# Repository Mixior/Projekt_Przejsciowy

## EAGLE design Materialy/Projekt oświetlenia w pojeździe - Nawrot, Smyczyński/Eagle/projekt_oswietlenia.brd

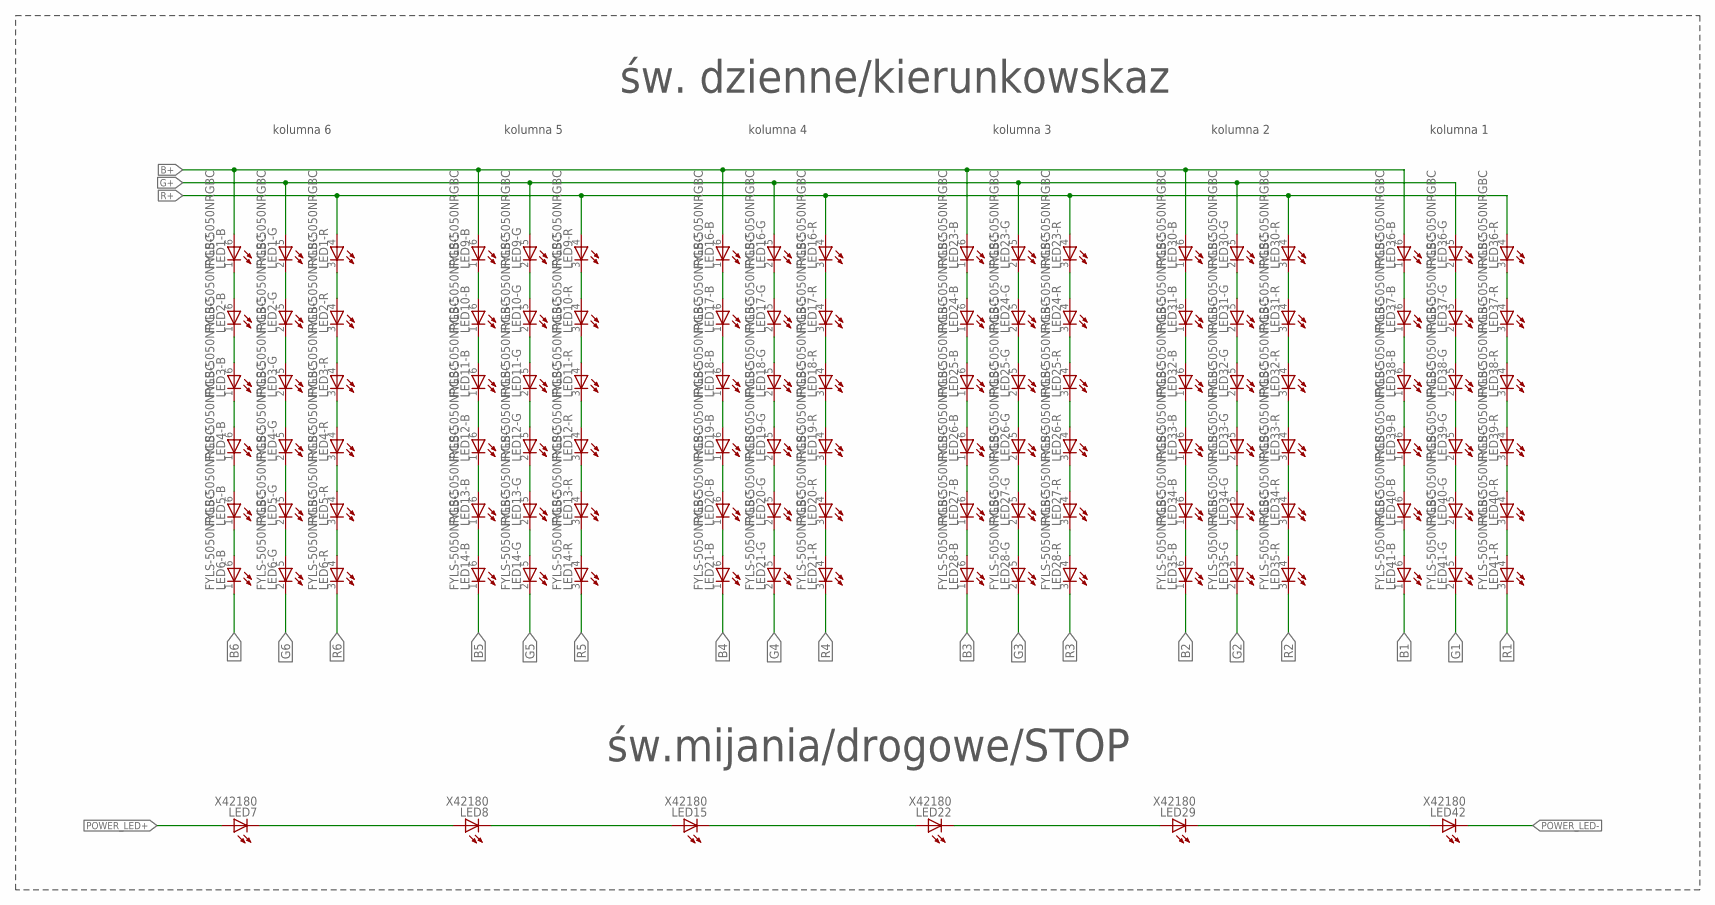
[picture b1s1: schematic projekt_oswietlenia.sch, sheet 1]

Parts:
LED1, LED2, LED3, LED4, LED5, LED6, LED9, LED10, LED11, LED12, LED13, LED14, LED16, LED17, LED18, LED19, LED20, LED21, LED23, LED24, LED25, LED26, LED27, LED28, LED30, LED31, LED32, LED33, LED34, LED35, LED36, LED37, LED38, LED39, LED40, LED41: FYLS-5050NRGBC; OVSTRGBBCR8
LED7, LED8, LED15, LED22, LED29, LED42: X42180; Z-POWER-LED-DOME-TYPE

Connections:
B1: LED41.1 (C); also elsewhere on the board
B2: LED35.1 (C); also elsewhere on the board
B3: LED28.1 (C); also elsewhere on the board
B4: LED21.1 (C); also elsewhere on the board
B5: LED14.1 (C); also elsewhere on the board
B6: LED6.1 (C); also elsewhere on the board
B+: LED1.6 (A), LED9.6 (A), LED16.6 (A), LED23.6 (A), LED30.6 (A), LED36.6 (A); also elsewhere on the board
G1: LED41.2 (C); also elsewhere on the board
G2: LED35.2 (C); also elsewhere on the board
G3: LED28.2 (C); also elsewhere on the board
G4: LED21.2 (C); also elsewhere on the board
G5: LED14.2 (C); also elsewhere on the board
G6: LED6.2 (C); also elsewhere on the board
G+: LED1.5 (A), LED9.5 (A), LED16.5 (A), LED23.5 (A), LED30.5 (A), LED36.5 (A); also elsewhere on the board
unnamed: LED13.3 (C), LED14.4 (A)
unnamed: LED13.2 (C), LED14.5 (A)
unnamed: LED13.1 (C), LED14.6 (A)
unnamed: LED12.3 (C), LED13.4 (A)
unnamed: LED12.2 (C), LED13.5 (A)
unnamed: LED12.1 (C), LED13.6 (A)
unnamed: LED11.1 (C), LED12.6 (A)
unnamed: LED11.2 (C), LED12.5 (A)
unnamed: LED11.3 (C), LED12.4 (A)
unnamed: LED10.3 (C), LED11.4 (A)
unnamed: LED10.2 (C), LED11.5 (A)
unnamed: LED29.C, LED42.A
unnamed: LED10.1 (C), LED11.6 (A)
unnamed: LED9.3 (C), LED10.4 (A)
unnamed: LED9.2 (C), LED10.5 (A)
unnamed: LED9.1 (C), LED10.6 (A)
unnamed: LED5.3 (C), LED6.4 (A)
unnamed: LED5.2 (C), LED6.5 (A)
unnamed: LED5.1 (C), LED6.6 (A)
unnamed: LED4.3 (C), LED5.4 (A)
unnamed: LED4.2 (C), LED5.5 (A)
unnamed: LED4.1 (C), LED5.6 (A)
unnamed: LED3.1 (C), LED4.6 (A)
unnamed: LED3.2 (C), LED4.5 (A)
unnamed: LED3.3 (C), LED4.4 (A)
unnamed: LED2.3 (C), LED3.4 (A)
unnamed: LED2.2 (C), LED3.5 (A)
unnamed: LED2.1 (C), LED3.6 (A)
unnamed: LED1.3 (C), LED2.4 (A)
unnamed: LED1.2 (C), LED2.5 (A)
unnamed: LED1.1 (C), LED2.6 (A)
unnamed: LED27.3 (C), LED28.4 (A)
unnamed: LED27.2 (C), LED28.5 (A)
unnamed: LED27.1 (C), LED28.6 (A)
unnamed: LED26.3 (C), LED27.4 (A)
unnamed: LED26.2 (C), LED27.5 (A)
unnamed: LED26.1 (C), LED27.6 (A)
unnamed: LED25.1 (C), LED26.6 (A)
unnamed: LED25.2 (C), LED26.5 (A)
unnamed: LED25.3 (C), LED26.4 (A)
unnamed: LED24.3 (C), LED25.4 (A)
unnamed: LED24.2 (C), LED25.5 (A)
unnamed: LED24.1 (C), LED25.6 (A)
unnamed: LED23.3 (C), LED24.4 (A)
unnamed: LED23.2 (C), LED24.5 (A)
unnamed: LED23.1 (C), LED24.6 (A)
unnamed: LED20.3 (C), LED21.4 (A)
unnamed: LED20.2 (C), LED21.5 (A)
unnamed: LED20.1 (C), LED21.6 (A)
unnamed: LED19.3 (C), LED20.4 (A)
unnamed: LED19.2 (C), LED20.5 (A)
unnamed: LED19.1 (C), LED20.6 (A)
unnamed: LED18.1 (C), LED19.6 (A)
unnamed: LED18.2 (C), LED19.5 (A)
unnamed: LED18.3 (C), LED19.4 (A)
unnamed: LED17.3 (C), LED18.4 (A)
unnamed: LED17.2 (C), LED18.5 (A)
unnamed: LED17.1 (C), LED18.6 (A)
unnamed: LED16.3 (C), LED17.4 (A)
unnamed: LED16.2 (C), LED17.5 (A)
unnamed: LED16.1 (C), LED17.6 (A)
unnamed: LED40.3 (C), LED41.4 (A)
unnamed: LED40.2 (C), LED41.5 (A)
unnamed: LED40.1 (C), LED41.6 (A)
unnamed: LED39.3 (C), LED40.4 (A)
unnamed: LED39.2 (C), LED40.5 (A)
unnamed: LED39.1 (C), LED40.6 (A)
unnamed: LED38.1 (C), LED39.6 (A)
unnamed: LED38.2 (C), LED39.5 (A)
unnamed: LED38.3 (C), LED39.4 (A)
unnamed: LED37.3 (C), LED38.4 (A)
unnamed: LED37.2 (C), LED38.5 (A)
unnamed: LED37.1 (C), LED38.6 (A)
unnamed: LED36.3 (C), LED37.4 (A)
unnamed: LED36.2 (C), LED37.5 (A)
unnamed: LED36.1 (C), LED37.6 (A)
unnamed: LED34.3 (C), LED35.4 (A)
unnamed: LED34.2 (C), LED35.5 (A)
unnamed: LED34.1 (C), LED35.6 (A)
unnamed: LED33.3 (C), LED34.4 (A)
unnamed: LED33.2 (C), LED34.5 (A)
unnamed: LED33.1 (C), LED34.6 (A)
unnamed: LED32.1 (C), LED33.6 (A)
unnamed: LED32.2 (C), LED33.5 (A)
unnamed: LED32.3 (C), LED33.4 (A)
unnamed: LED31.3 (C), LED32.4 (A)
unnamed: LED31.2 (C), LED32.5 (A)
unnamed: LED31.1 (C), LED32.6 (A)
unnamed: LED30.3 (C), LED31.4 (A)
unnamed: LED30.2 (C), LED31.5 (A)
unnamed: LED30.1 (C), LED31.6 (A)
unnamed: LED22.C, LED29.A
unnamed: LED15.C, LED22.A
unnamed: LED8.C, LED15.A
unnamed: LED7.C, LED8.A
POWER_LED+: LED7.A; also elsewhere on the board
POWER_LED-: LED42.C; also elsewhere on the board
R1: LED41.3 (C); also elsewhere on the board
R2: LED35.3 (C); also elsewhere on the board
R3: LED28.3 (C); also elsewhere on the board
R4: LED21.3 (C); also elsewhere on the board
R5: LED14.3 (C); also elsewhere on the board
R6: LED6.3 (C); also elsewhere on the board
R+: LED1.4 (A), LED9.4 (A), LED16.4 (A), LED23.4 (A), LED30.4 (A), LED36.4 (A); also elsewhere on the board

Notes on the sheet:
św. dzienne/kierunkowskaz
kolumna 6
kolumna 5
kolumna 4
kolumna 3
kolumna 2
kolumna 1
św.mijania/drogowe/STOP

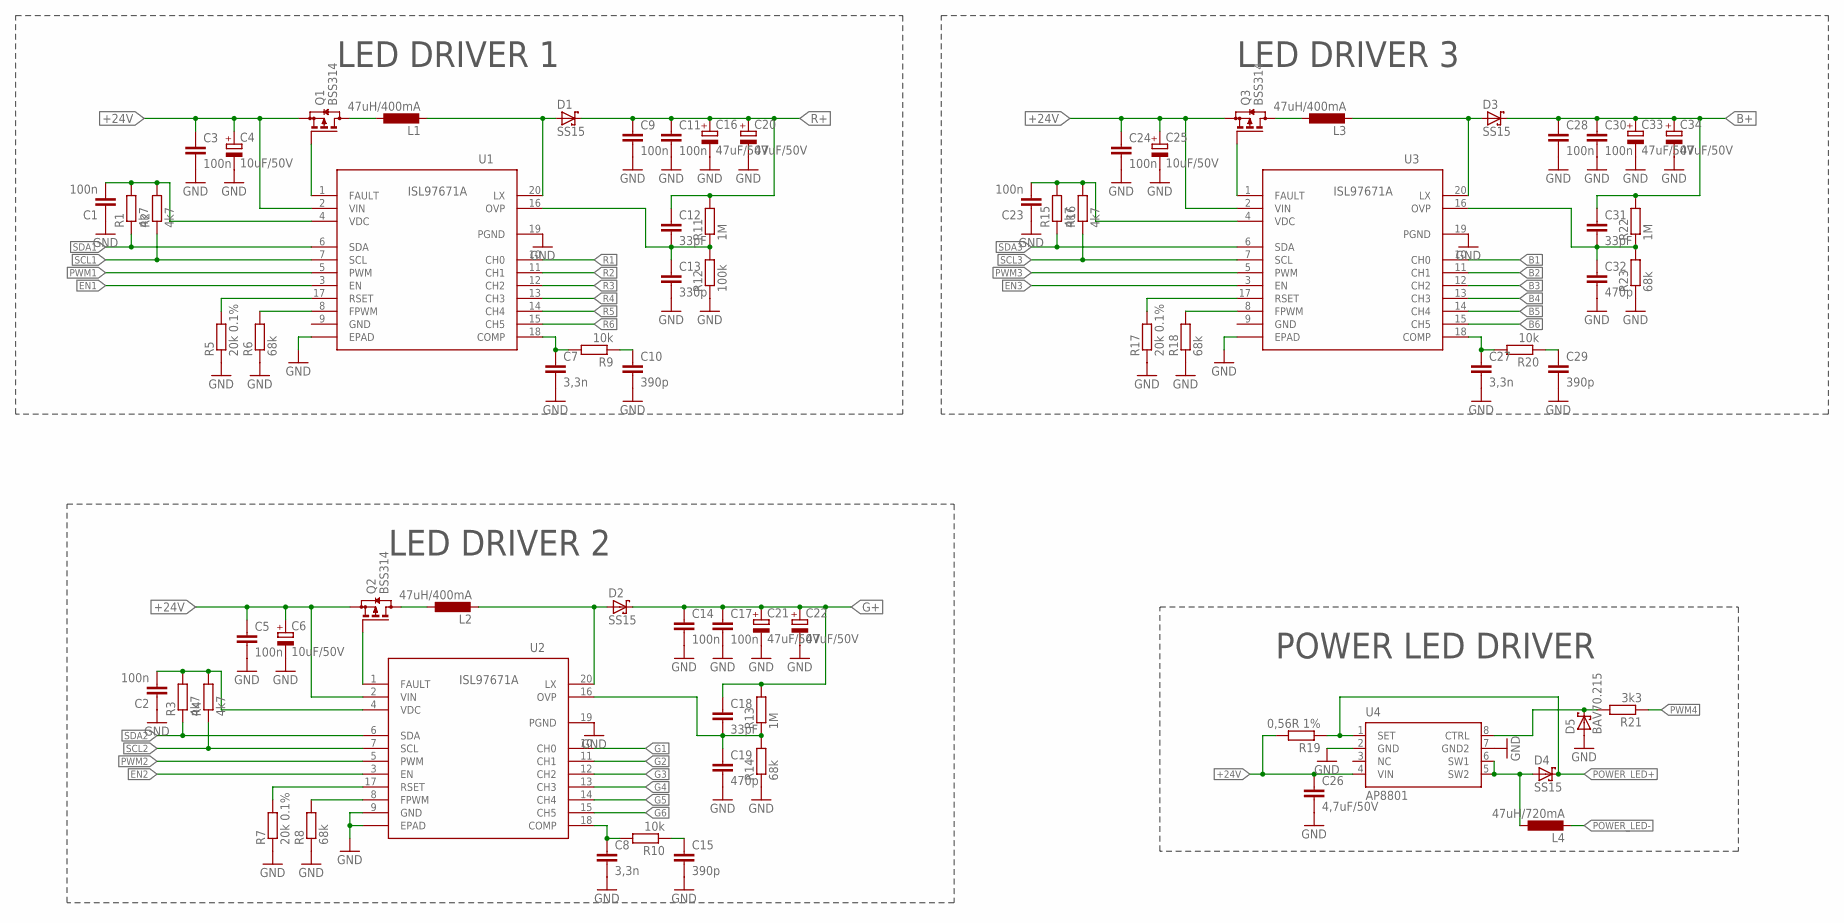
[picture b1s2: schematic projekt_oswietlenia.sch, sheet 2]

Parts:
C1, C2, C3, C5, C9, C11, C14, C17, C23, C24, C28, C30: 100n; C0603
C4, C6, C25: 10uF/50V; 153CLV-0605
C7, C8, C27: 3,3n; C0603
C10, C15, C29: 390p; C0603
C12, C18, C31: 33pF; C0603
C13: 330p; C0603
C16, C20, C21, C22, C33, C34: 47uF/50V; 153CLV-0605
C19, C32: 470p; C0603
C26: 4,7uF/50V; C0603
D1, D2, D3, D4: SS15; DO-214AC
D5: BAV70.215; SOT23
L1, L2, L3: 47uH/400mA; POWER-CHOKE_WE-TPC
L4: 47uH/720mA; POWER-CHOKE_WE-TPC
Q1, Q2, Q3: BSS314; SOT23
R1, R2, R3, R4, R15, R16: 4k7; R0603
R5, R7, R17: 20k 0.1%; R0603
R6, R8, R14, R18, R23: 68k; R0603
R9, R10, R20: 10k; R0603
R11, R13, R22: 1M; R0603
R12: 100k; R0603
R19: 0,56R 1%; R0603
R21: 3k3; R0603
U1, U2, U3: ISL97671A; QFN20
U4: AP8801; SOP-08

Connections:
+24V: C3.1, C4.+, C5.1, C6.+, C24.1, C25.+, C26.1, Q1.2 (S), Q2.2 (S), Q3.2 (S), R19.2, U1.2 (VIN), U2.2 (VIN), U3.2 (VIN), U4.4 (VIN); also elsewhere on the board
B1: U3.10 (CH0); also elsewhere on the board
B2: U3.11 (CH1); also elsewhere on the board
B3: U3.12 (CH2); also elsewhere on the board
B4: U3.13 (CH3); also elsewhere on the board
B5: U3.14 (CH4); also elsewhere on the board
B6: U3.15 (CH5); also elsewhere on the board
B+: C28.1, C30.1, C31.1, C33.+, C34.+, D3.C, R22.2; also elsewhere on the board
EN1: U1.3 (EN); also elsewhere on the board
EN2: U2.3 (EN); also elsewhere on the board
EN3: U3.3 (EN); also elsewhere on the board
G1: U2.10 (CH0); also elsewhere on the board
G2: U2.11 (CH1); also elsewhere on the board
G3: U2.12 (CH2); also elsewhere on the board
G4: U2.13 (CH3); also elsewhere on the board
G5: U2.14 (CH4); also elsewhere on the board
G6: U2.15 (CH5); also elsewhere on the board
G+: C14.1, C17.1, C18.1, C21.+, C22.+, D2.C, R13.2; also elsewhere on the board
GND: C1.1, C2.1, C3.2, C4.-, C5.2, C6.-, C7.2, C8.2, C9.2, C10.2, C11.2, C13.2, C14.2, C15.2, C16.-, C17.2, C19.2, C20.-, C21.-, C22.-, C23.1, C24.2, C25.-, C26.2, C27.2, C28.2, C29.2, C30.2, C32.2, C33.-, C34.-, D5.1 (A), R5.1, R6.1, R7.1, R8.1, R12.1, R14.1, R17.1, R18.1, R23.1, U1.9 (GND), U1.19 (PGND), U1.EPAD, U2.9 (GND), U2.19 (PGND), U2.EPAD, U3.9 (GND), U3.19 (PGND), U3.EPAD, U4.2 (GND), U4.7 (GND2); also elsewhere on the board
unnamed: D4.A, L4.1, U4.5 (SW2), U4.6 (SW1)
unnamed: D5.3 (C), R21.2, U4.8 (CTRL)
unnamed: Q3.1 (G), U3.1 (FAULT)
unnamed: L3.1, Q3.3 (D)
unnamed: D3.A, L3.2, U3.20 (LX)
unnamed: C31.2, C32.1, R22.1, R23.2, U3.16 (OVP)
unnamed: C27.1, R20.2, U3.18 (COMP)
unnamed: C29.1, R20.1
unnamed: R18.2, U3.8 (FPWM)
unnamed: R17.2, U3.17 (RSET)
unnamed: Q1.1 (G), U1.1 (FAULT)
unnamed: L1.1, Q1.3 (D)
unnamed: D1.A, L1.2, U1.20 (LX)
unnamed: C12.2, C13.1, R11.1, R12.2, U1.16 (OVP)
unnamed: C7.1, R9.2, U1.18 (COMP)
unnamed: C10.1, R9.1
unnamed: R6.2, U1.8 (FPWM)
unnamed: C23.2, R15.2, R16.2, U3.4 (VDC)
unnamed: R5.2, U1.17 (RSET)
unnamed: C1.2, R1.2, R2.2, U1.4 (VDC)
unnamed: Q2.1 (G), U2.1 (FAULT)
unnamed: L2.1, Q2.3 (D)
unnamed: D2.A, L2.2, U2.20 (LX)
unnamed: C18.2, C19.1, R13.1, R14.2, U2.16 (OVP)
unnamed: C8.1, R10.2, U2.18 (COMP)
unnamed: C15.1, R10.1
unnamed: R8.2, U2.8 (FPWM)
unnamed: R7.2, U2.17 (RSET)
unnamed: C2.2, R3.2, R4.2, U2.4 (VDC)
POWER_LED+: D4.C, R19.1, U4.1 (SET); also elsewhere on the board
POWER_LED-: L4.2; also elsewhere on the board
PWM1: U1.5 (PWM); also elsewhere on the board
PWM2: U2.5 (PWM); also elsewhere on the board
PWM3: U3.5 (PWM); also elsewhere on the board
PWM4: R21.1; also elsewhere on the board
R1: U1.10 (CH0); also elsewhere on the board
R2: U1.11 (CH1); also elsewhere on the board
R3: U1.12 (CH2); also elsewhere on the board
R4: U1.13 (CH3); also elsewhere on the board
R5: U1.14 (CH4); also elsewhere on the board
R6: U1.15 (CH5); also elsewhere on the board
R+: C9.1, C11.1, C12.1, C16.+, C20.+, D1.C, R11.2; also elsewhere on the board
SCL1: R2.1, U1.7 (SCL); also elsewhere on the board
SCL2: R4.1, U2.7 (SCL); also elsewhere on the board
SCL3: R16.1, U3.7 (SCL); also elsewhere on the board
SDA1: R1.1, U1.6 (SDA); also elsewhere on the board
SDA2: R3.1, U2.6 (SDA); also elsewhere on the board
SDA3: R15.1, U3.6 (SDA); also elsewhere on the board

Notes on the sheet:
LED DRIVER 2
LED DRIVER 3
POWER LED DRIVER
LED DRIVER 1

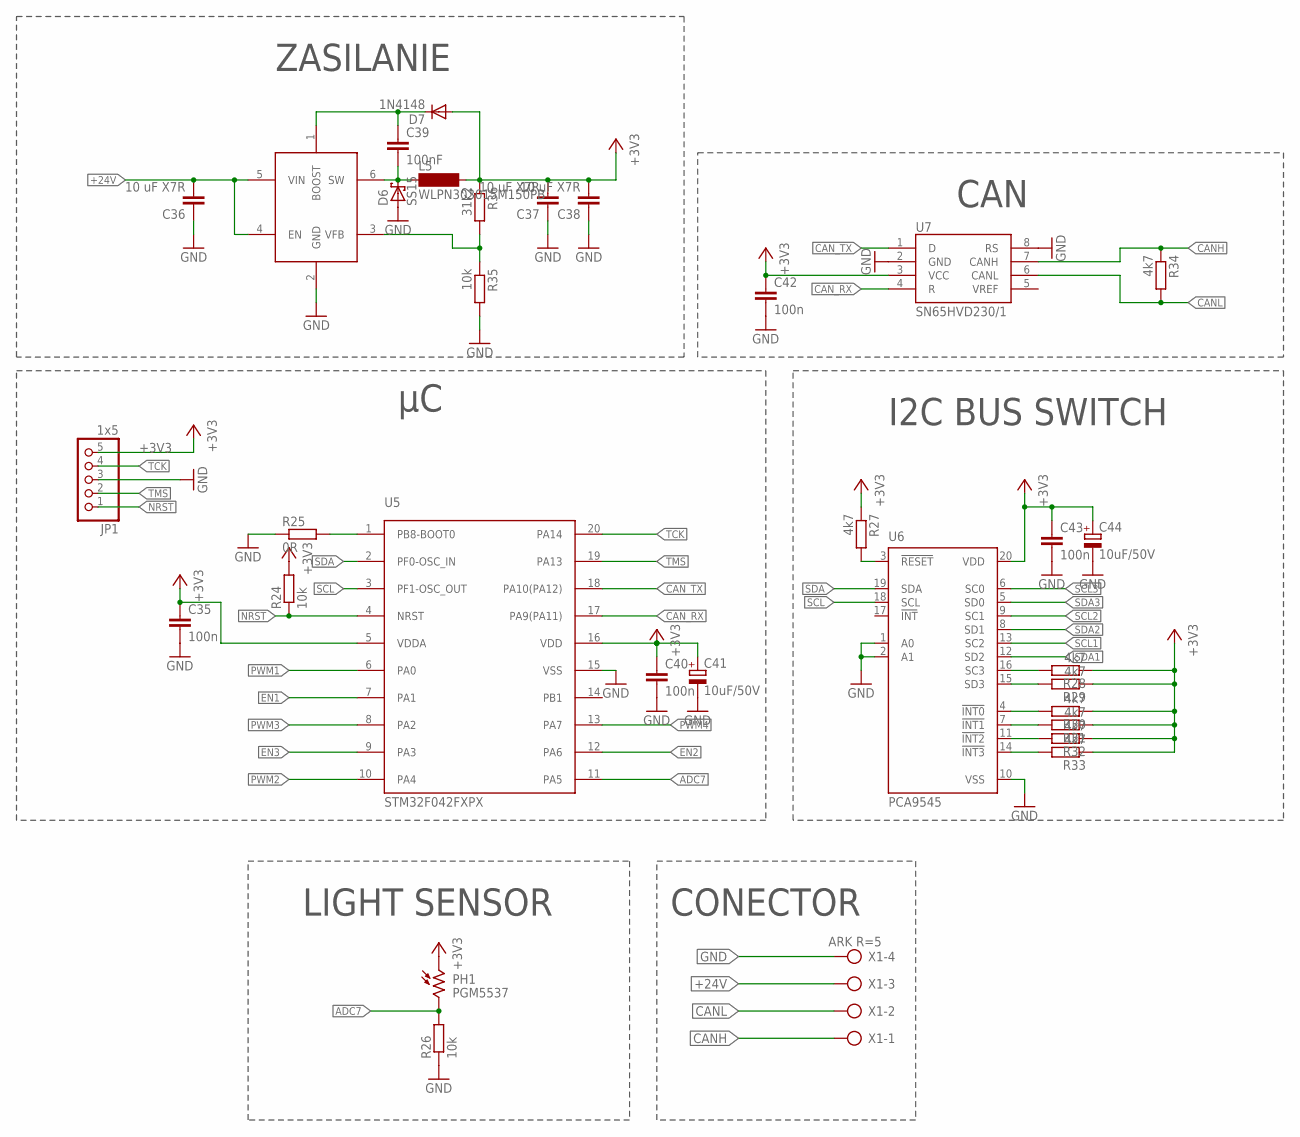
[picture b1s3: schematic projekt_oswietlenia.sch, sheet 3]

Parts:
C35, C40, C42, C43: 100n; C0603
C36, C37, C38: 10 uF X7R; C0603
C39: 100nF; C0603
C41, C44: 10uF/50V; 153CLV-0605
D6: SS15; DO-214AC
D7: 1N4148; SMB
IC1: MCP16301/H; SOT23-6
JP1: 1x5; 1X05
L5: WLPN303015M150PB; MS50
PH1: PGM5537; VT800
R24, R26, R35: 10k; R0603
R25: 0R; R0603
R27, R28, R29, R30, R31, R32, R33, R34: 4k7; R0603
R36: 31k2; R0603
U5: STM32F042FXPX; TSSOP20
U6: PCA9545; SO20W
U7: SN65HVD230/1; SO8
X1: ARK R=5; AK500/4

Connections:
+3V3: C35.1, C37.2, C38.2, C40.1, C41.+, C42.1, C43.1, C44.+, D7.A, JP1.5, L5.2, PH1.1, R24.2, R27.1, R28.1, R29.1, R30.1, R31.1, R32.1, R33.1, R36.1, U5.5 (VDDA), U5.16 (VDD), U6.20 (VDD), U7.3 (VCC)
+24V: C36.2, IC1.4 (EN), IC1.5 (VIN), X1.3; also elsewhere on the board
ADC7: PH1.2, R26.2, U5.11 (PA5)
CANH: R34.1, U7.7 (CANH), X1.1
CANL: R34.2, U7.6 (CANL), X1.2
CAN_RX: U5.17 (PA9(PA11)), U7.4 (R)
CAN_TX: U5.18 (PA10(PA12)), U7.1 (D)
EN1: U5.7 (PA1); also elsewhere on the board
EN2: U5.12 (PA6); also elsewhere on the board
EN3: U5.9 (PA3); also elsewhere on the board
GND: C35.2, C36.1, C37.1, C38.1, C40.2, C41.-, C42.2, C43.2, C44.-, D6.A, IC1.2 (GND), JP1.3, R25.1, R26.1, R35.2, U5.15 (VSS), U6.1 (A0), U6.2 (A1), U6.10 (VSS), U7.2 (GND), U7.8 (RS), X1.4; also elsewhere on the board
unnamed: C39.1, D7.C, IC1.1 (BOOST)
unnamed: R33.2, U6.14 (!INT3)
unnamed: R32.2, U6.11 (!INT2)
unnamed: R31.2, U6.7 (!INT1)
unnamed: R30.2, U6.4 (!INT0)
unnamed: R29.2, U6.15 (SD3)
unnamed: R28.2, U6.16 (SC3)
unnamed: R27.2, U6.3 (!RESET)
unnamed: C39.2, D6.C, IC1.6 (SW), L5.1
unnamed: IC1.3 (VFB), R35.1, R36.2
unnamed: R25.2, U5.1 (PB8-BOOT0)
NRST: JP1.1, R24.1, U5.4 (NRST)
PWM1: U5.6 (PA0); also elsewhere on the board
PWM2: U5.10 (PA4); also elsewhere on the board
PWM3: U5.8 (PA2); also elsewhere on the board
PWM4: U5.13 (PA7); also elsewhere on the board
SCL: U5.3 (PF1-OSC_OUT), U6.18 (SCL)
SCL1: U6.13 (SC2); also elsewhere on the board
SCL2: U6.9 (SC1); also elsewhere on the board
SCL3: U6.6 (SC0); also elsewhere on the board
SDA: U5.2 (PF0-OSC_IN), U6.19 (SDA)
SDA1: U6.12 (SD2); also elsewhere on the board
SDA2: U6.8 (SD1); also elsewhere on the board
SDA3: U6.5 (SD0); also elsewhere on the board
TCK: JP1.4, U5.20 (PA14)
TMS: JP1.2, U5.19 (PA13)

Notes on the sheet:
CAN
LIGHT SENSOR
CONECTOR
ZASILANIE
I2C BUS SWITCH

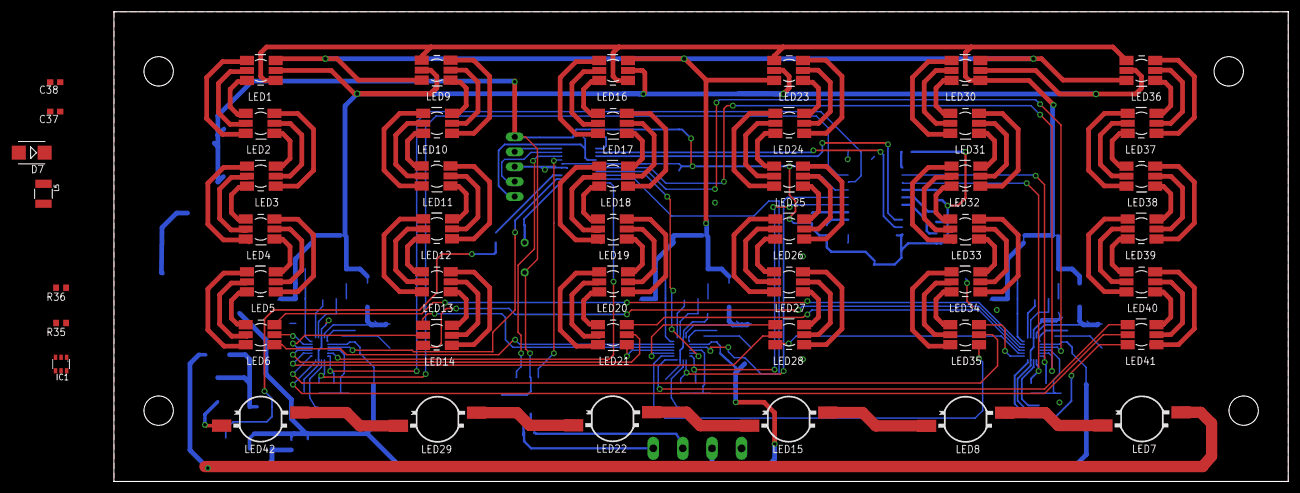
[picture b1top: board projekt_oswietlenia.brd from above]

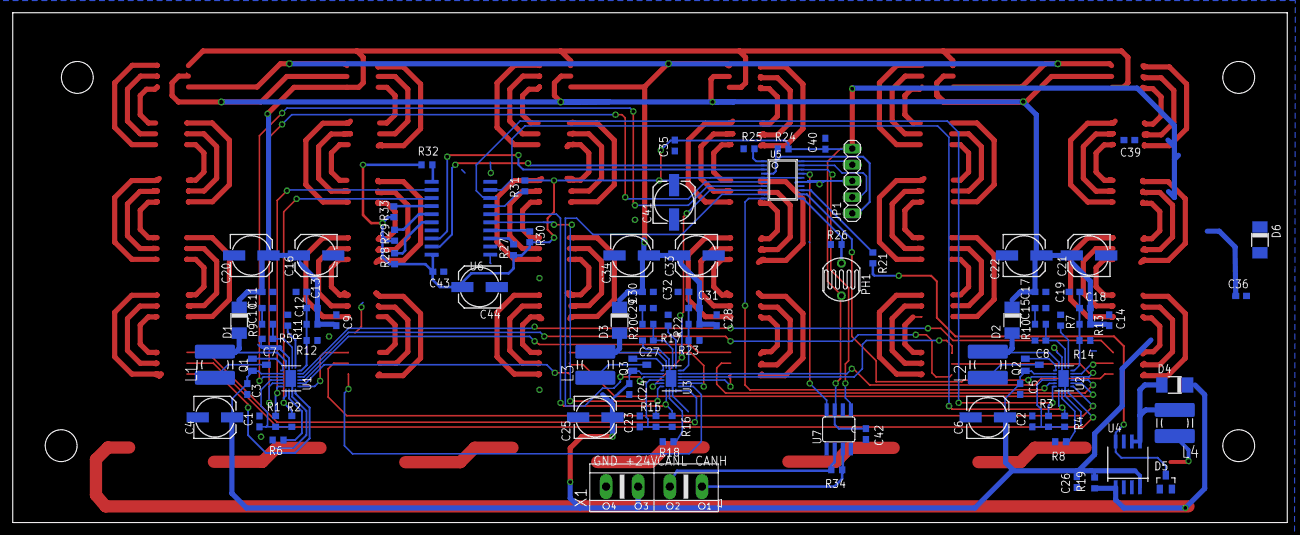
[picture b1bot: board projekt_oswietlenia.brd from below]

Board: 2 copper layers, 200.0 x 80.0 mm, 148 parts (99 on the bottom side), 184 nets.

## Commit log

2019-04-17 Materialy
2019-04-17 Usuniecie zipow
